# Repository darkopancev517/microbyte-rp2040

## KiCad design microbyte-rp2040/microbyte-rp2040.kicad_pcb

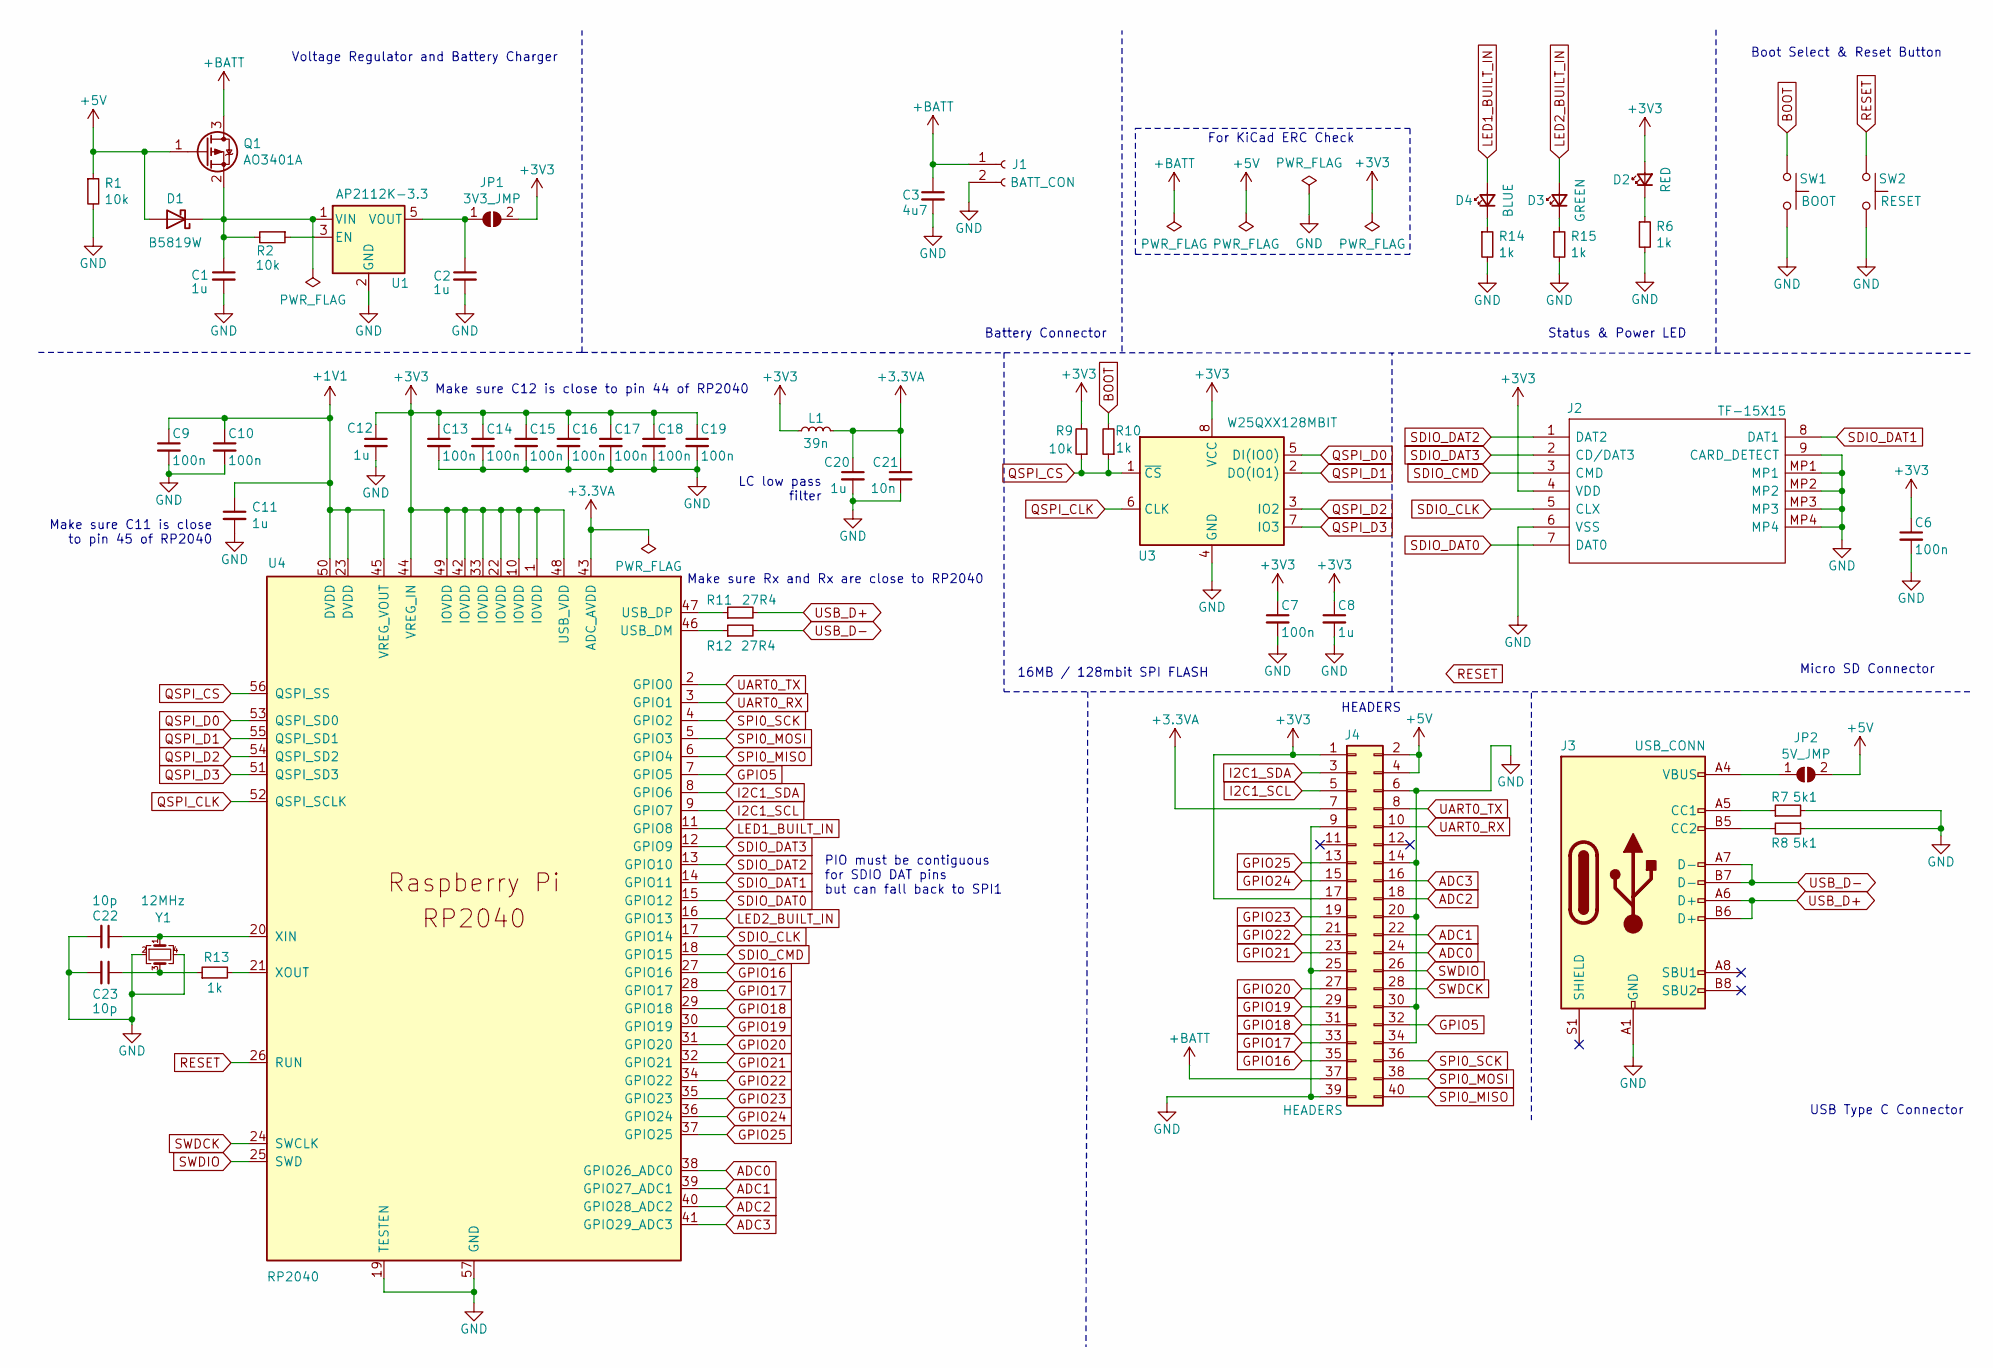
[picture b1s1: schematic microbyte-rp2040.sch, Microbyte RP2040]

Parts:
C1, C2, C8: 1u; C_0603_1608Metric; LCSC C15849
C3: 4u7; C_0603_1608Metric; LCSC C19666
C6, C7, C9, C10, C13, C14, C15, C16, C17, C18, C19: 100n; C_0402_1005Metric; LCSC C1525
C11, C12, C20: 1u; C_0402_1005Metric; LCSC C52923
C21: 10n; C_0402_1005Metric; LCSC C15195
C22, C23: 10p; C_0402_1005Metric; LCSC C32949
D1: B5819W; D_SOD-123; LCSC C8598
D2: RED; LED_0603_1608Metric; LCSC C2286
D3: GREEN; LED_0603_1608Metric; LCSC C72043
D4: BLUE; LED_0603_1608Metric; LCSC C72041
J1: BATT_CON; JST_PH_S2B-PH-SM4-TB_1x02-1MP_P2.00mm_Horizontal; LCSC C722680
J2: TF-15X15; TF15X15; Manufacturer_Part_Number TF-15X15; LCSC C111196
J3: USB_CONN; USB_C_Receptacle_HRO_TYPE-C-31-M-12; LCSC C165948
J4: HEADERS; PinHeader_2x20_P2.54mm_Vertical
JP1: 3V3_JMP; SolderJumper-2_P1.3mm_Open_RoundedPad1.0x1.5mm
JP2: 5V_JMP; SolderJumper-2_P1.3mm_Open_RoundedPad1.0x1.5mm
L1: 39n; L_0603_1608Metric; LCSC C74308
Q1: AO3401A; SOT-23; LCSC C700954
R1, R2: 10k; R_0603_1608Metric; LCSC C25804
R6, R10, R13, R14, R15: 1k; R_0402_1005Metric; LCSC C11702
R7, R8: 5k1; R_0402_1005Metric; LCSC C25905
R9: 10k; R_0402_1005Metric; LCSC C25744
R11, R12: 27R4; R_0402_1005Metric; LCSC C31439
SW1: BOOT; SW_SPST_TL3342; LCSC C318889
SW2: RESET; SW_SPST_TL3342; LCSC C318889
U1: AP2112K-3.3; SOT-23-5; LCSC C51118
U3: W25QXX128MBIT; SOIC-8_5.23x5.23mm_P1.27mm; LCSC C97521
U4: RP2040; RP2040-QFN-56; LCSC C2040
Y1: 12MHz; Crystal_SMD_3225-4Pin_3.2x2.5mm; LCSC C9002

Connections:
+1V1: C9.1, C10.1, C11.1, U4.23 (DVDD), U4.45 (VREG_VOUT), U4.50 (DVDD)
+3.3VA: C20.1, C21.1, J4.7, L1.2, U4.43 (ADC_AVDD)
+3V3: C6.1, C7.1, C8.1, C12.1, C13.1, C14.1, C15.1, C16.1, C17.1, C18.1, C19.1, D2.2 (A), J2.4 (VDD), J4.1, J4.17, JP1.2 (B), L1.1, R9.2, U3.8 (VCC), U4.1 (IOVDD), U4.10 (IOVDD), U4.22 (IOVDD), U4.33 (IOVDD), U4.42 (IOVDD), U4.44 (VREG_IN), U4.48 (USB_VDD), U4.49 (IOVDD)
+5V: D1.2 (A), J4.2, J4.4, JP2.2 (B), Q1.1 (G), R1.1
+BATT: C3.1, J1.1, J4.37, Q1.3 (D)
ADC0: J4.24, U4.38 (GPIO26_ADC0)
ADC1: J4.22, U4.39 (GPIO27_ADC1)
ADC2: J4.18, U4.40 (GPIO28_ADC2)
ADC3: J4.16, U4.41 (GPIO29_ADC3)
BOOT: R10.2, SW1.1
GND: C1.2, C2.2, C3.2, C6.2, C7.2, C8.2, C9.2, C10.2, C11.2, C12.2, C13.2, C14.2, C15.2, C16.2, C17.2, C18.2, C19.2, C20.2, C21.2, C22.2, C23.2, J1.2, J2.6 (VSS), J2.9 (CARD_DETECT), J2.MP1, J2.MP2, J2.MP3, J2.MP4, J3.A1 (GND), J3.A12 (GND), J3.B1 (GND), J3.B12 (GND), J4.6, J4.9, J4.14, J4.20, J4.25, J4.30, J4.34, J4.39, R1.2, R6.2, R7.2, R8.1, R14.2, R15.2, SW1.2, SW2.2, U1.2 (GND), U3.4 (GND), U4.19 (TESTEN), U4.57 (GND), Y1.2, Y1.4
GPIO5: J4.32, U4.7 (GPIO5)
GPIO16: J4.35, U4.27 (GPIO16)
GPIO17: J4.33, U4.28 (GPIO17)
GPIO18: J4.31, U4.29 (GPIO18)
GPIO19: J4.29, U4.30 (GPIO19)
GPIO20: J4.27, U4.31 (GPIO20)
GPIO21: J4.23, U4.32 (GPIO21)
GPIO22: J4.21, U4.34 (GPIO22)
GPIO23: J4.19, U4.35 (GPIO23)
GPIO24: J4.15, U4.36 (GPIO24)
GPIO25: J4.13, U4.37 (GPIO25)
I2C1_SCL: J4.5, U4.9 (GPIO7)
I2C1_SDA: J4.3, U4.8 (GPIO6)
LED1_BUILT_IN: D4.2 (A), U4.11 (GPIO8)
LED2_BUILT_IN: D3.2 (A), U4.16 (GPIO13)
unnamed: C1.1, D1.1 (K), Q1.2 (S), R2.2, U1.1 (VIN)
unnamed: C2.1, JP1.1 (A), U1.5 (VOUT)
unnamed: C22.1, U4.20 (XIN), Y1.1
unnamed: C23.1, R13.1, Y1.3
unnamed: D2.1 (K), R6.1
unnamed: D3.1 (K), R15.1
unnamed: D4.1 (K), R14.1
unnamed: J3.A4 (VBUS), J3.A9 (VBUS), J3.B4 (VBUS), J3.B9 (VBUS), JP2.1 (A)
unnamed: J3.A5 (CC1), R7.1
unnamed: J3.B5 (CC2), R8.2
unnamed: R2.1, U1.3 (EN)
unnamed: R11.1, U4.47 (USB_DP)
unnamed: R12.1, U4.46 (USB_DM)
unnamed: R13.2, U4.21 (XOUT)
QSPI_CLK: U3.6 (CLK), U4.52 (QSPI_SCLK)
QSPI_CS: R9.1, R10.1, U3.1 (~CS), U4.56 (QSPI_SS)
QSPI_D0: U3.5 (DI(IO0)), U4.53 (QSPI_SD0)
QSPI_D1: U3.2 (DO(IO1)), U4.55 (QSPI_SD1)
QSPI_D2: U3.3 (IO2), U4.54 (QSPI_SD2)
QSPI_D3: U3.7 (IO3), U4.51 (QSPI_SD3)
RESET: SW2.1, U4.26 (RUN)
SDIO_CLK: J2.5 (CLX), U4.17 (GPIO14)
SDIO_CMD: J2.3 (CMD), U4.18 (GPIO15)
SDIO_DAT0: J2.7 (DAT0), U4.15 (GPIO12)
SDIO_DAT1: J2.8 (DAT1), U4.14 (GPIO11)
SDIO_DAT2: J2.1 (DAT2), U4.13 (GPIO10)
SDIO_DAT3: J2.2 (CD/DAT3), U4.12 (GPIO9)
SPI0_MISO: J4.40, U4.6 (GPIO4)
SPI0_MOSI: J4.38, U4.5 (GPIO3)
SPI0_SCK: J4.36, U4.4 (GPIO2)
SWDCK: J4.28, U4.24 (SWCLK)
SWDIO: J4.26, U4.25 (SWD)
UART0_RX: J4.10, U4.3 (GPIO1)
UART0_TX: J4.8, U4.2 (GPIO0)
USB_D+: J3.A6 (D+), J3.B6 (D+), R11.2
USB_D-: J3.A7 (D-), J3.B7 (D-), R12.2

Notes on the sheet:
Make sure C12 is close to pin 44 of RP2040
Voltage Regulator and Battery Charger
Status & Power LED
Boot Select & Reset Button
USB Type C Connector
Micro SD Connector
HEADERS
Make sure Rx and Rx are close to RP2040
Make sure C11 is close to pin 45 of RP2040
LC low pass filter
16MB / 128mbit SPI FLASH
PIO must be contiguous for SDIO DAT pins but can fall back to SPI1
For KiCad ERC Check
Battery Connector

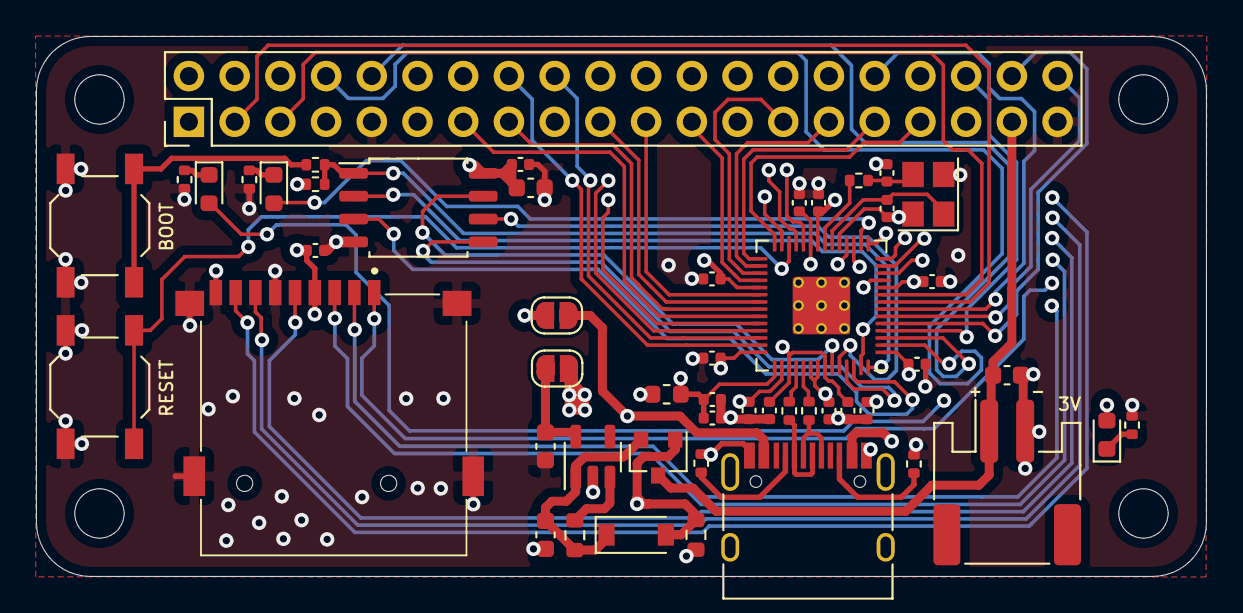
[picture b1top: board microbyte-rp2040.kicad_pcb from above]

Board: 4 copper layers, 65.0 x 30.0 mm, 51 parts (0 on the bottom side), 62 nets.

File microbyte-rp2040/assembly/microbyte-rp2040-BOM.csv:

Comment,Designator,Footprint,LCSC
"1u","C1,C2,C8","Capacitor_SMD:C_0603_1608Metric","C15849"
"1u","C11,C12,C20","Capacitor_SMD:C_0402_1005Metric","C52923"
"100n","C6,C7,C9,C10,C13,C14,C15,C16,C17,C18,C19","Capacitor_SMD:C_0402_1005Metric","C1525"
"10n","C21","Capacitor_SMD:C_0402_1005Metric","C15195"
"10p","C22,C23","Capacitor_SMD:C_0402_1005Metric","C32949"
"4u7","C3,C4","Capacitor_SMD:C_0603_1608Metric","C19666"
"B5819W","D1","Diode_SMD:D_SOD-123","C8598"
"YELLOW","D2","LED_SMD:LED_0603_1608Metric","C72038"
"RED","D4","LED_SMD:LED_0603_1608Metric","C2286"
"GREEN","D5","LED_SMD:LED_0603_1608Metric","C72043"
"BLUE","D6","LED_SMD:LED_0603_1608Metric","C72041"
"BATT_CON","J1","Connector_JST:JST_PH_S2B-PH-SM4-TB_1x02-1MP_P2.00mm_Horizontal","C722680"
"TF-15X15","J2","SOFNG:TF15X15","C111196"
"USB_CONN","J3","Connector_USB:USB_C_Receptacle_HRO_TYPE-C-31-M-12","C165948"
"HEADERS","J4","Connector_PinHeader_2.54mm:PinHeader_2x20_P2.54mm_Vertical",""
"39n","L1","Inductor_SMD:L_0603_1608Metric","C74308"
"AO3401A","Q1","Package_TO_SOT_SMD:SOT-23","C700954"
"10k","R1,R2","Resistor_SMD:R_0603_1608Metric","C25804"
"27R4","R11,R12","Resistor_SMD:R_0402_1005Metric","C31439"
"2k","R3","Resistor_SMD:R_0603_1608Metric","C22975"
"1k","R4,R6,R10,R13,R14,R15","Resistor_SMD:R_0402_1005Metric","C11702"
"5k1","R7,R8","Resistor_SMD:R_0402_1005Metric","C25905"
"10k","R9","Resistor_SMD:R_0402_1005Metric","C25744"
"BOOT","SW1","Button_Switch_SMD:Panasonic_EVQPUL_EVQPUC","C79175"
"RESET","SW2","Button_Switch_SMD:Panasonic_EVQPUL_EVQPUC","C79175"
"AP2112K-3.3","U1","Package_TO_SOT_SMD:SOT-23-5","C51118"
"MCP73831-2-OT","U2","Package_TO_SOT_SMD:SOT-23-5","C424093"
"W25QXX128MBIT","U3","Package_SO:SOIC-8_5.23x5.23mm_P1.27mm","C97521"
"RP2040","U4","RP2040:RP2040-QFN-56","C2040"
"12MHz","Y1","Crystal:Crystal_SMD_3225-4Pin_3.2x2.5mm","C9002"

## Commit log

2021-08-13 microbyte-v1.0
2021-08-19 microbyte-rp2040-v1.1
2021-08-20 microbyte-rp2040-v1.1 released
2021-08-23 remove tooling holes

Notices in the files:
microbyte-rp2040/microbyte-rp2040.kicad_pcb:
License: MIT - Copyright 2018 StudioPieters®
